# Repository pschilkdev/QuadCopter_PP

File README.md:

# QuadCopter_PP<br>
Main Repository for all code, schematics and PCB board layouts for the Quadcopter Project.<br>
Personal Project 2015/16 IICS<br>
<br>
All code for various Pic Microcontrollers programmed in either XC8 or XC32. <br>
All schematics and PCB board layouts designed in KiCad. <br>
<br>
Naming Scheme for Code:<br>
&nbsp;PPQCU_{RC/QCU}_[Processor Name]<br>
<br>
<b>Key:</b><br>
&nbsp;PPQCU: <br>
&nbsp;&nbsp;Project Handle (<b>P</b>ersonal <b>P</b>roject <b>Q</b>uad<b>C</b>opter <b>C</b>ontrol <b>U</b>nit)<br>
&nbsp;RC / QCU:<br>
&nbsp;&nbsp;Location of the MicroController associated with the programm.<br>
&nbsp;&nbsp;&nbsp;RC: The MicroController is located on the Remote Control<br>
&nbsp;&nbsp;&nbsp;QCU: The MicroController is located on the Control Unit on the Quadcopter<br>
&nbsp;Processor Name:<br>
&nbsp;&nbsp;Name of the Processor<br>
<br>
<br>	
<b>Programs Included:</b><br>
&nbsp;PPQCU_CU_MAIN:<br>
&nbsp;&nbsp;MicroController:<br>
&nbsp;&nbsp;&nbsp;PIC32MX120F064H<br>
&nbsp;&nbsp;Language/Compiler:<br>
&nbsp;&nbsp;&nbsp;Programmed in C using the XC32 Complier.<br>
&nbsp;&nbsp;MicroController Purpose:<br>
&nbsp;&nbsp;&nbsp;Main processor on the Control Unit<br>
<br>
&nbsp;PPQCU_CU_BATSENSE:<br>
&nbsp;&nbsp;MicroController:<br>
&nbsp;&nbsp;&nbsp;PIC12F1840<br>
&nbsp;&nbsp;Language/Compiler:<br>
&nbsp;&nbsp;&nbsp;Programmed in C using the XC8 Complier<br>
&nbsp;&nbsp;MicroController Purpose:<br>
&nbsp;&nbsp;&nbsp;Battery Level Sensing, and low battery warning<br>
<br>
&nbsp;PPQCU_CU_INTERFACE:<br>
&nbsp;&nbsp;MicroController:<br>
&nbsp;&nbsp;&nbsp;PIC12F1840<br>
&nbsp;&nbsp;Language/Compiler:<br>
&nbsp;&nbsp;&nbsp;Programmed in C using the XC8 Complier<br>
&nbsp;&nbsp;MicroController Purpose:<br>
&nbsp;&nbsp;&nbsp;Interfacing to the ESC and, in turn, the motors.<br>
<br>
&nbsp;PPQCU_CU_LIGHTS:<br>
&nbsp;&nbsp;MicroController:<br>
&nbsp;&nbsp;&nbsp;PIC12F1840<br>
&nbsp;&nbsp;Language/Compiler:<br>
&nbsp;&nbsp;&nbsp;Programmed in C using the XC8 Complier<br>
&nbsp;&nbsp;Controller Purpose:<br>
&nbsp;&nbsp;&nbsp;UI on the QuadCopter<br>
<br>	
&nbsp;PPQCU_RC_REMOTE:<br>
&nbsp;&nbsp;MicroController:<br>
&nbsp;&nbsp;&nbsp;PIC18F26K22<br>
&nbsp;&nbsp;Language/Compiler:<br>
&nbsp;&nbsp;&nbsp;Programmed in C using the XC8 Complier<br>
&nbsp;&nbsp;MicroController Purpose:<br>
&nbsp;&nbsp;&nbsp;Main Processor on the Remote Controller<br>
<br>
<b>Licensing/Attribution:</b><br>
NRF wireless handler used (modified): tinkerer.eu port by g4lvanix: https://github.com/g4lvanix/NRF-wireless

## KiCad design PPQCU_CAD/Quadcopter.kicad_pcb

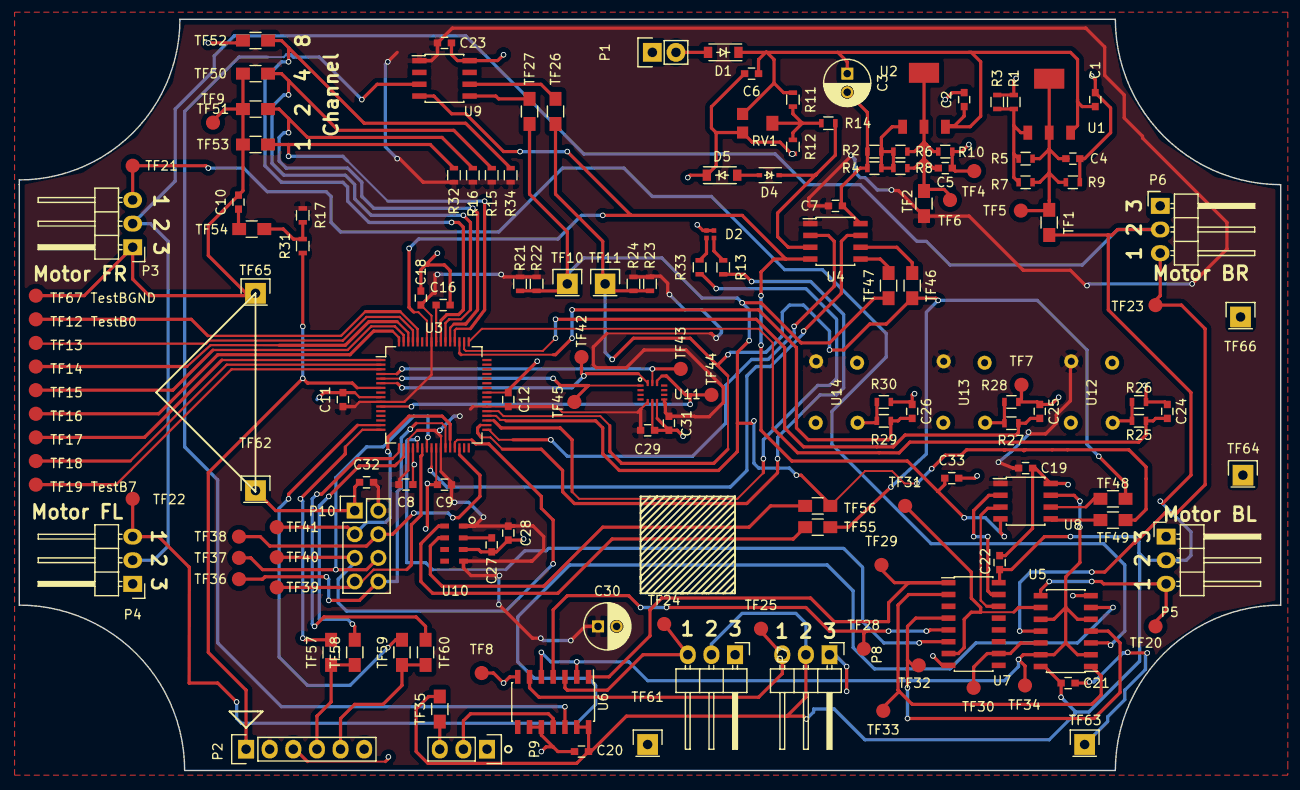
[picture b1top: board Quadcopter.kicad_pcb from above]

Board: 2 copper layers, 135.6 x 80.8 mm, 155 parts (0 on the bottom side), 87 nets.

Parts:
C1, C2, C6, C7, C8, C9, C10, C11, C12, C18, C19, C20, C21, C22, C23, C27, C28, C29, C31, C32, C33: 0u1; C_0603
C3: 100uf; C_Radial_D5_L11_P2
C4, C5: 1uf; C_0603
C16, C24, C25, C26: 10u; C_0603
C30: 10u; C_Radial_D5_L11_P2
D1: D; SOD-123
D2: Dual_LED; dualLED
D4: 3.4V; SOD-323
D5: TV; SOD-123
P1: Battery; Pin_Header_Straight_1x02
P2: DEBUG; Pin_Header_Straight_1x06
P3: Serv1; Pin_Header_Angled_1x03
P4: Serv2; Pin_Header_Angled_1x03
P5: Serv3; Pin_Header_Angled_1x03
P6: Serv4; Pin_Header_Angled_1x03
P7: SecServ1; Pin_Header_Angled_1x03
P8: SecServ2; Pin_Header_Angled_1x03
P9: ws2812; Pin_Header_Straight_1x03
P10: CONN_02X04; Pin_Header_Straight_2x04
R1, R14, R31: 1K; R_0603
R2: 540R; R_0603
R3, R4, R7, R8, R11, R12, R22, R24: TV; R_0603
R5, R6: 330R; R_0603
R9: 680R; R_0603
R10: 470R; R_0603
R13, R33: 50R; R_0603
R15, R16, R17, R21, R23, R26, R28, R30, R32, R34: 10K; R_0603
R25, R27, R29: 100K; R_0603
RV1: 100K; EVM3Y
TF1: 5V; R_0805_HandSoldering
TF2: 3V; R_0805_HandSoldering
TF4, TF7, TF8, TF9: GND; Measurement_Point_Round-SMD-Pad_Small
TF5: 5V; Measurement_Point_Round-SMD-Pad_Small
TF6: 3V3; Measurement_Point_Round-SMD-Pad_Small
TF10: i2cDAT; Pin_Header_Straight_1x01
TF11: i2cCLK; Pin_Header_Straight_1x01
TF12: TestB0; Measurement_Point_Round-SMD-Pad_Small
TF13: TestB1; Measurement_Point_Round-SMD-Pad_Small
TF14: TestB2; Measurement_Point_Round-SMD-Pad_Small
TF15: TestB3; Measurement_Point_Round-SMD-Pad_Small
TF16: TestB4; Measurement_Point_Round-SMD-Pad_Small
TF17: TestB5; Measurement_Point_Round-SMD-Pad_Small
TF18: TestB6; Measurement_Point_Round-SMD-Pad_Small
TF19: TestB7; Measurement_Point_Round-SMD-Pad_Small
TF20: s3; Measurement_Point_Round-SMD-Pad_Small
TF21: s1; Measurement_Point_Round-SMD-Pad_Small
TF22: s2; Measurement_Point_Round-SMD-Pad_Small
TF23: s4; Measurement_Point_Round-SMD-Pad_Small
TF24: ss1; Measurement_Point_Round-SMD-Pad_Small
TF25: ss2; Measurement_Point_Round-SMD-Pad_Small
TF26, TF27: li; R_0805_HandSoldering
TF28: u6; Measurement_Point_Round-SMD-Pad_Small
TF29: u5; Measurement_Point_Round-SMD-Pad_Small
TF30: u4; Measurement_Point_Round-SMD-Pad_Small
TF31: u3; Measurement_Point_Round-SMD-Pad_Small
TF32: u2; Measurement_Point_Round-SMD-Pad_Small
TF33: u1; Measurement_Point_Round-SMD-Pad_Small
TF34: ga; Measurement_Point_Round-SMD-Pad_Small
TF35: L5; R_0805_HandSoldering
TF36: wIRQ; Measurement_Point_Round-SMD-Pad_Small
TF37: wMOSI; Measurement_Point_Round-SMD-Pad_Small
TF38: wCSN; Measurement_Point_Round-SMD-Pad_Small
TF39: wMISO; Measurement_Point_Round-SMD-Pad_Small
TF40: wSCK; Measurement_Point_Round-SMD-Pad_Small
TF41: wCE; Measurement_Point_Round-SMD-Pad_Small
TF42: aMOSI; Measurement_Point_Round-SMD-Pad_Small
TF43: aSCK; Measurement_Point_Round-SMD-Pad_Small
TF44: aCSB; Measurement_Point_Round-SMD-Pad_Small
TF45: MISO; Measurement_Point_Round-SMD-Pad_Small
TF46, TF47: bi; R_0805_HandSoldering
TF48, TF49: ii; R_0805_HandSoldering
TF50: a3; R_0805_HandSoldering
TF51: a2; R_0805_HandSoldering
TF52: a4; R_0805_HandSoldering
TF53: a1; R_0805_HandSoldering
TF54: cd; R_0805_HandSoldering
TF55, TF56: pi; R_0805_HandSoldering
TF57: d1; R_0805_HandSoldering
TF58: d2; R_0805_HandSoldering
TF59: c1; R_0805_HandSoldering
TF60: c2; R_0805_HandSoldering
TF61, TF62, TF63, TF64, TF65, TF66: GND; Pin_Header_Straight_1x01
TF67: TestBGND; Measurement_Point_Round-SMD-Pad_Small
U1, U2: LM317; SOT-233-4
U3: PIC32MX120F064H-I/PT; LQFP-64_10x10mm_Pitch0.5mm
U4, U8, U9: PIC12F1840; SOIC-8_3.9x4.9mm_Pitch1.27mm
U5, U6: 74HC08; SOIC-14_3.9x8.7mm_Pitch1.27mm
U7: 74HC4017; SOIC-16_3.9x9.9mm_Pitch1.27mm
U10: MPL3115A2
U11: BMI160
U12, U13, U14: BTN; B3F-1000

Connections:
+3V3: C7.2, C8.2, C9.1, C11.1, C12.1, C18.1, C19.2, C23.2, C28.1, C29.1, C30.1, C31.1, C32.2, P2.2, P10.2, R15.1, R16.1, R17.1, R21.1, R22.1, R23.1, R24.1, R32.1, R34.1, TF2.2, U3.10, U3.19, U3.26, U3.38, U3.57, U4.1, U8.1, U9.1, U10.1, U10.4, U11.5, U11.8, U12.3, U13.3, U14.3
+5V: C20.1, C21.1, C22.1, P3.2, P4.2, P5.2, P6.2, P7.2, P8.2, TF1.2, TF35.2, U5.14, U6.13, U6.14, U7.16
+BATT: C1.1, C2.1, C3.1, C6.1, D1.1, R11.1, RV1.1, U1.3, U2.3
BTN1: C24.1, R25.2, U3.49
BTN2: C25.1, R27.2, U3.50
BTN3: C26.1, R29.2, U3.51
GND: C1.2, C2.2, C3.2, C4.2, C5.2, C6.2, C7.1, C8.1, C9.2, C10.2, C11.2, C12.2, C16.2, C18.2, C19.1, C20.2, C21.2, C22.2, C23.1, C24.2, C25.2, C26.2, C27.2, C28.2, C29.2, C30.2, C31.2, C32.1, C33.2, D2.3, D2.4, D5.1, P1.1, P2.3, P3.1, P4.1, P5.1, P6.1, P7.1, P8.1, P9.1, P10.1, R1.2, R2.2, R3.2, R4.2, R9.2, R10.2, R12.2, R26.2, R28.2, R30.2, RV1.3, TF4.1, TF7.1, TF8.1, TF9.1, TF50.1, TF51.1, TF52.1, TF53.1, TF61.1, TF62.1, TF63.1, TF64.1, TF65.1, TF66.1, TF67.1, U3.9, U3.20, U3.25, U3.41, U4.8, U5.7, U6.7, U6.9, U6.10, U7.8, U8.8, U9.8, U10.3, U11.6, U11.7
MCLR: P2.1, R31.1, U3.7
unnamed: C4.1, R5.1, R7.1, R9.1, TF1.1, TF5.1, U1.2, U1.4
unnamed: C5.1, R6.1, R8.1, R10.1, TF2.1, TF6.1, U2.2, U2.4
unnamed: C10.1, TF54.2
unnamed: C16.1, U3.56
unnamed: C27.1, U10.2
unnamed: D1.2, P1.2
unnamed: D2.1, R33.1
unnamed: D2.2, R13.1
unnamed: D4.1, R14.1, U4.3
unnamed: D4.2, D5.2
unnamed: P2.4, TF57.1, TF58.1
unnamed: P2.5, TF59.1, TF60.1
unnamed: P3.3, TF21.1, U5.3
unnamed: P4.3, TF22.1, U5.6
unnamed: P5.3, TF20.1, U5.8
unnamed: P6.3, TF23.1, U5.11
unnamed: P7.3, TF24.1, U6.3
unnamed: P8.3, TF25.1, U6.6
unnamed: P9.3, TF35.1
unnamed: R1.1, R3.1, R5.2, R7.2, U1.1
unnamed: R2.1, R4.1, R6.2, R8.2, U2.1
unnamed: R11.2, R12.1, R14.2, RV1.2
unnamed: R15.2, TF50.2, U3.54
unnamed: R16.2, TF51.2, U3.53
unnamed: R17.2, R31.2, TF54.1
unnamed: R25.1, R26.1, U12.1
unnamed: R27.1, R28.1, U13.1
unnamed: R29.1, R30.1, U14.1
unnamed: R32.2, TF53.2, U3.52
unnamed: R34.2, TF52.2, U3.55
unnamed: TF26.1, U9.6
unnamed: TF27.1, U9.5
unnamed: TF28.1, U6.4, U7.5
unnamed: TF29.1, U6.1, U7.1
unnamed: TF30.1, U5.12, U7.10
unnamed: TF31.1, U5.9, U7.7
unnamed: TF32.1, U5.4, U7.4
unnamed: TF33.1, U5.1, U7.2
unnamed: TF34.1, U5.2, U5.5, U5.10, U5.13, U6.2, U6.5, U8.7
unnamed: TF46.2, U4.6
unnamed: TF47.2, U4.5
unnamed: TF48.2, U8.6
unnamed: TF49.2, U8.5
unnamed: TF55.1, U10.8
unnamed: TF56.1, U10.7
unnamed: U7.14, U8.3
unnamed: U7.15, U8.2
ProgC_1: TF59.2, U3.15
ProgC_2: TF60.2, U3.17
ProgD_1: TF57.2, U3.16
ProgD_2: TF58.2, U3.18
SCLR: C33.1, U3.58, U4.4, U8.4, U9.4
ServIntRD: U3.21, U7.6
T0: TF12.1, U3.60
T1: TF13.1, U3.61
T2: TF14.1, U3.62
T3: TF15.1, U3.63
T4: TF16.1, U3.64
T5: TF17.1, U3.1
T6: TF18.1, U3.2
T7: TF19.1, U3.3
WS_out: P9.2, U6.11
WS_sig: U6.12, U9.3
aCSB: TF44.1, U3.11, U11.12
aMISO: TF45.1, U3.5, U11.1
aMOSI: TF42.1, U3.6, U11.14
aSCK: TF43.1, U3.4, U11.13
batled_in: U3.33, U4.2
batled_out1: R13.2, U3.34
batled_out2: R33.2, U3.35
battWarn: U3.24, U4.7
i2cCLK: R23.2, R24.2, TF11.1, TF26.2, TF46.1, TF48.1, TF55.2, U3.37
i2cDAT: R21.2, R22.2, TF10.1, TF27.2, TF47.1, TF49.1, TF56.2, U3.36
wCE: P10.3, TF41.1, U3.28
wCSN: P10.4, TF38.1, U3.30
wIRQ: P10.8, TF36.1, U3.27
wMISO: P10.7, TF39.1, U3.22
wMOSI: P10.6, TF37.1, U3.23
wSCK: P10.5, TF40.1, U3.29

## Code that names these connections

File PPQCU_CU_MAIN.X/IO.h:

/* 
 * File:   IO.h
 * Author: Philipp
 *
 * Created on February 21, 2016, 1:55 PM
 */

#ifndef IO_H
#define	IO_H

#ifdef	__cplusplus
extern "C" {
#endif

    //NRF SPI Bus
#define IO_wMISO_TRI TRISBbits.TRISB9
#define IO_wMISO_REG 0b0101
#define IO_wMOSI_TRI TRISBbits.TRISB1
#define IO_wMOSI_REG RPB10Rbits.RPB10R
#define IO_wCE_TRI TRISBbits.TRISB13
#define IO_wCE LATBbits.LATB13
#define IO_wSCK_TRI TRISBbits.TRISB14
#define IO_wCSN_TRI TRISBbits.TRISB15
#define IO_wCSN LATBbits.LATB15

    //BMI SPI Bus
#define IO_aMISO_TRI TRISGbits.TRISG7
#define IO_aMISO_REG 0b0001
#define IO_aMOSI_TRI TRISGbits.TRISG8
#define IO_aMOSI_REG RPG8Rbits.RPG8R
#define IO_aSCK_TRI TRISGbits.TRISG6
#define IO_aCSB_TRI TRISBbits.TRISB5
#define IO_aCSB LATBbits.LATB5
  
    //BatWarn
#define IO_battWarn1_TRI TRISBbits.TRISB11
#define IO_battWarn1 PORTBbits.RB11
#define IO_battWarn2_TRI TRISFbits.TRISF3
#define IO_battWarn2 PORTFbits.RF3

#define IO_battLed1_TRI TRISFbits.TRISF2
#define IO_battLed1 LATFbits.LATF2
#define IO_battLed2_TRI TRISFbits.TRISF6  
#define IO_battLed2 LATFbits.LATF6
/*NOTE: ERROR IN PIC32MX120F064H HEADER
PIN F6 NOT INCLUDED EVEN THOUGH ACTUAL PIN IN DATASHEET
CHANGE THE FOLLOWING CODE IN p32mx120f064h.h:

CHANGE PORTF UNION TO:
	[...]
    unsigned RF4:1;
    unsigned RF5:1;
	unsigned RF6:1;
    unsigned :1;
    unsigned RF8:1;
	[...]
	
CHANGE LATF UNION TO:
	[...]
    unsigned LATF4:1;
    unsigned LATF5:1;
	unsigned LATF6:1;
    unsigned :1;
    unsigned LATF8:1;
	[...]

CHANGE TRISF UNION TO:
    [...]
    unsigned TRISF4:1;
    unsigned TRISF5:1;
	unsigned TRISF6:1;
    unsigned :1;
    unsigned TRISF8:1;
    [...]
*/


#define IO_SCLEAR_TRI TRISFbits.TRISF0
#define IO_SCLEAR LATFbits.LATF0
 
#define IO_DEBUG_TRI TRISE
#define IO_DEBUG_R PORTE
#define IO_DEBUG_RB PORTEbits
#define IO_DEBUG_W LATESET

#define IO_B1_TRI TRISDbits.TRISD1
#define IO_B1 PORTDbits.RD1
#define IO_B2_TRI TRISDbits.TRISD2
#define IO_B2 PORTDbits.RD2
#define IO_B3_TRI TRISDbits.TRISD3
#define IO_B3 PORTDbits.RD3
    
#define IO_C1_TRI TRISDbits.TRISD4
#define IO_C1 PORTDbits.RD4
#define IO_C2_TRI TRISDbits.TRISD5
#define IO_C2 PORTDbits.RD5
#define IO_C3_TRI TRISDbits.TRISD6
#define IO_C3 PORTDbits.RD6
#define IO_C4_TRI TRISDbits.TRISD7
#define IO_C4 PORTDbits.RD7
    /*          
        //BUTTON INPUT & CHANNEL SELECT BITS 
        TRISD = 0b11111110;  
     */


#ifdef	__cplusplus
}
#endif

#endif	/* IO_H */

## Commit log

2015-12-28 Initial README
2015-12-28 Fixed readme formatting
2015-12-28 Added PPQCU_CU_MAIN Project and updated gitignore
2015-12-30 Added intial config files, settings to be confirmed and untested
2015-12-31 Added Global Variables to MAIN conifg.h
2015-12-31 Updated gitignore for GDrive
2015-12-31 Oscillator Configuration. Untested...
2015-12-31 Started work on SPI. INIT completed but untested
2015-12-31 Oscillator Setup for Interface Chip
2015-12-31 Created BATSENSE and LIGHTS project, using osc setup from INTERFACE
2015-12-31 Created Initial Programm Structure for INTERFACE Chip
2015-12-31 Added missing handshake function
2015-12-31 Fixed another missing method
2016-01-02 Updated gitignore to include logic analyzer setups
2016-01-02 Added first draft of servo interfacing. Untested
2016-01-02 Created empty Remote Control Project
2016-01-02 Setup general programm structure and flow for BatSense
2016-01-02 Added ADC code. Untested
2016-01-02 Added IO config
2016-01-02 Fixed general programm structure
2016-01-02 Fixed config/pragmas/includes
2016-01-02 Finished SPI interface. Untested
2016-01-03 Quick Reformat
2016-01-03 Finished NRF INIT sequence. Untested
2016-01-03 Updated Programming Port Select bits. Do not programm without tthis change
2016-01-03 Continued Work on NRF. Still Untested
2016-01-04 Finished I2C interpret and bit stepthrough for LIGHTS
2016-01-22 Tested SPI Bus, Basic function present. Updated Gitignore for test-projects
2016-01-26 SPI BUS WORKING
2016-01-26 Fixed issue with SPI read: Wait for buffer to be written to be SPIxBUF
2016-01-26 First succesfull read and write to NRF plus random work on NRF.c
2016-01-26 Made NRF config registers easier to edit, plus random additions to NRF.c
2016-01-28 Updated init_IO for NRF and test code for NRF SPI
2016-01-28 Cleaned csn bit toogle and started work on transmit and receive code
2016-01-28 Started work on BMI SPI interface, UNTESTED
2016-01-28 Updated init_IO for BMI
2016-01-29 Added all registers to BMI.h
2016-01-29 Added methods to read Data from BMI
2016-01-30 Fixed Complier errors with BMI read_multiple
2016-01-30 added method to check for completion of TX
2016-02-04 Fixed SPI channel selection
2016-02-04 Setup IO for Main file + General cleanup
2016-02-08 Started work on I2C interface
2016-02-08 Added Quadcopter Config Files
2016-02-10 Finished I2C Config Register Headers
2016-02-10 Changed values to hex, fixed naming scheme
2016-02-10 Fixed naming scheme for IIC init flags
2016-02-10 First draft of basic IIC methods
2016-02-11 Fixed I2C Adress
2016-02-11 Added intial files for MPL interface
2016-02-11 Changed acces to status of IIC
2016-02-11 Added missing ack function and finished receive and transmit routine. Untested
2016-02-12 Finished IIC init procedure, ready to test IIC interface
2016-02-13 Changed programming channel to ICS_PGx1
2016-02-13 Fixed small typo
2016-02-13 Fixed small error in IIC status routine
2016-02-13 Started work on I2C Quadcopter Protocol
2016-02-13 Continued work on first draft of Quadcopter I2C Protocol
2016-02-14 Tested output routine, working
2016-02-14 Fixed timeout. Interface code is now fully tested. Drafted I2C interface, untested
2016-02-20 PP Debug Session, tried hacking together for demo, did not work. Code not functional, nor pretty. Only kept for reference
2016-02-20 Updated gitignore for KiCad
2016-02-20 Intital commit of board and schematic. Rev. 1. Sent to Fab
2016-02-20 4 layer version of board. Not used. Only kept for historical purposes
2016-02-20 Removed Servo Interface Ready, as it would cause a 5V signal on the pic32mx120
2016-02-20 Tied Inverted advance of Johnson Counter to ground, as floating input causes bad output signals
2016-02-20 Worked on Interface Chip, changed to trigger on receive instead of timed loop
2016-02-20 Fixed motor I2C interface
2016-02-21 Inital layout for debug methods
2016-02-21 Fixed small typos
2016-02-21 Worked on battery level recorvery setup
2016-02-21 Fixed Battery Level Warn Signals to main Processor
2016-02-21 Fixed small typing error
2016-02-21 Fixed/Cleaned up IO handling
2016-02-21 Finished first draft of Bat Sense, has to be tested
2016-02-21 Pulled over neccesary code from PPdebug manually, compiles but not tested
2016-02-22 SAving remote calibration to eeprom now, untested
2016-02-23 Added config file
2016-02-23 fixed funciton prototypes
2016-02-24 Added credit for NRF work to readme
2016-02-24 Pulled over files from libary and added modification notes
2016-02-24 Ported libary over for remote control chip
2016-02-24 Pulled over files for Main Processor
2016-02-24 Added note about broken header file
2016-02-25 Upadted libary handling for KiCad, Saving lbaries for parts and footprints in seperate repo now
2016-02-26 Fixed spelling error
2016-02-26 Fixed small overlaps/visual errors in layout
2016-02-28 Changed the way IIC transmits are polled. Now a failure to acknoledge by the slave will not cause the system to get stuck
